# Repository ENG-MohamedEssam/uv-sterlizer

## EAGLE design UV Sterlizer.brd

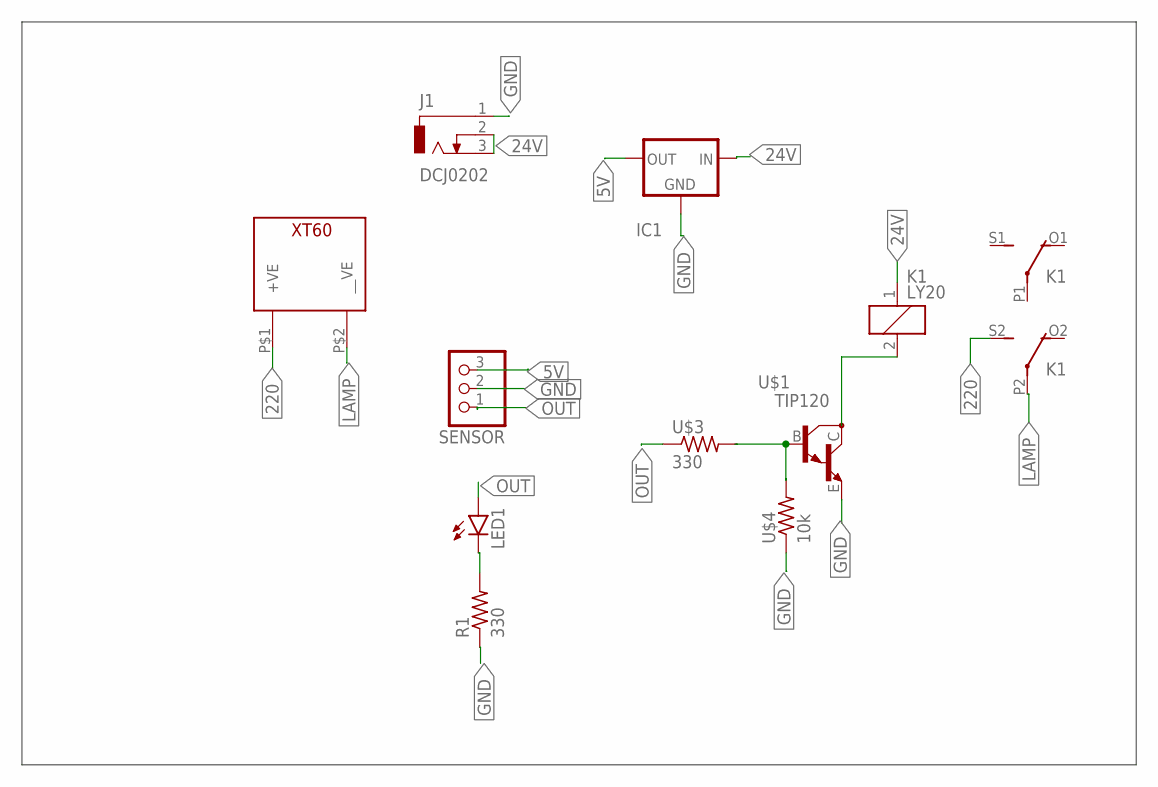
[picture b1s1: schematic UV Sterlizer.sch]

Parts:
IC1: 78XX-METAL; TO3-79
J1: DCJ0202
K1: LY20
LED1: LED5MM
R1: 330; 0204/7
SENSOR: PINHD-1X3; 1X03
U$1: TIP120
U$3: 330; 0207/10
U$4: 10k; 0207/10
U$5: XT60_CONNECTOR; XT60

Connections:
5V: IC1.1 (OUT), SENSOR.3
24V: IC1.3 (IN), J1.2, J1.3, K1.1
220: K1.S2 (S), U$5.P$1 (+VE)
GND: IC1.2 (GND), J1.1, R1.1, SENSOR.2, U$1.E, U$4.1
LAMP: K1.P2, U$5.P$2 (__VE)
unnamed: K1.2, U$1.C
unnamed: U$1.B, U$3.2, U$4.2
unnamed: LED1.K (C), R1.2
OUT: LED1.A, SENSOR.1, U$3.1

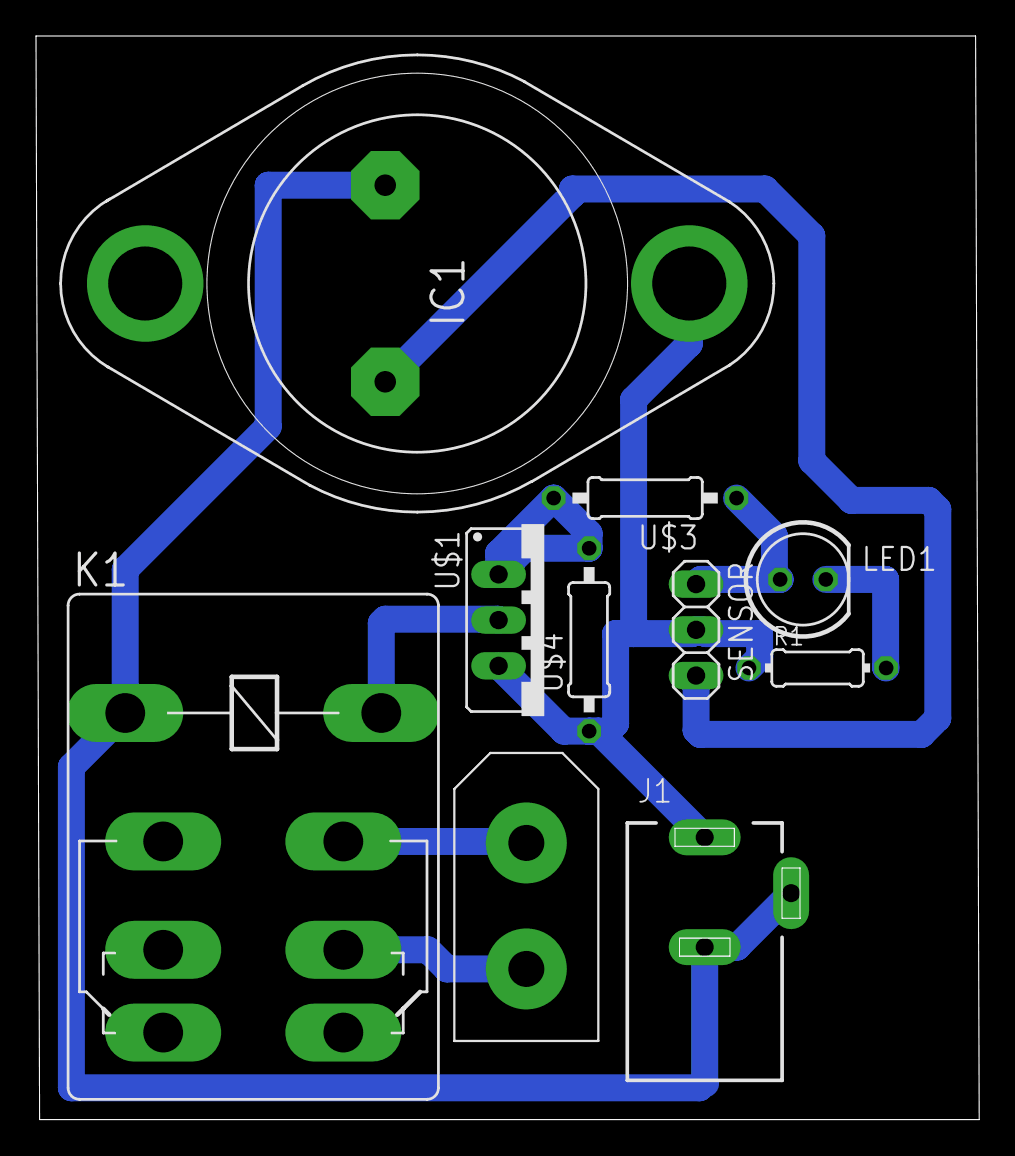
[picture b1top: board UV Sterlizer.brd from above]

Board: 2 copper layers, 52.4 x 60.2 mm, 10 parts (0 on the bottom side), 9 nets.

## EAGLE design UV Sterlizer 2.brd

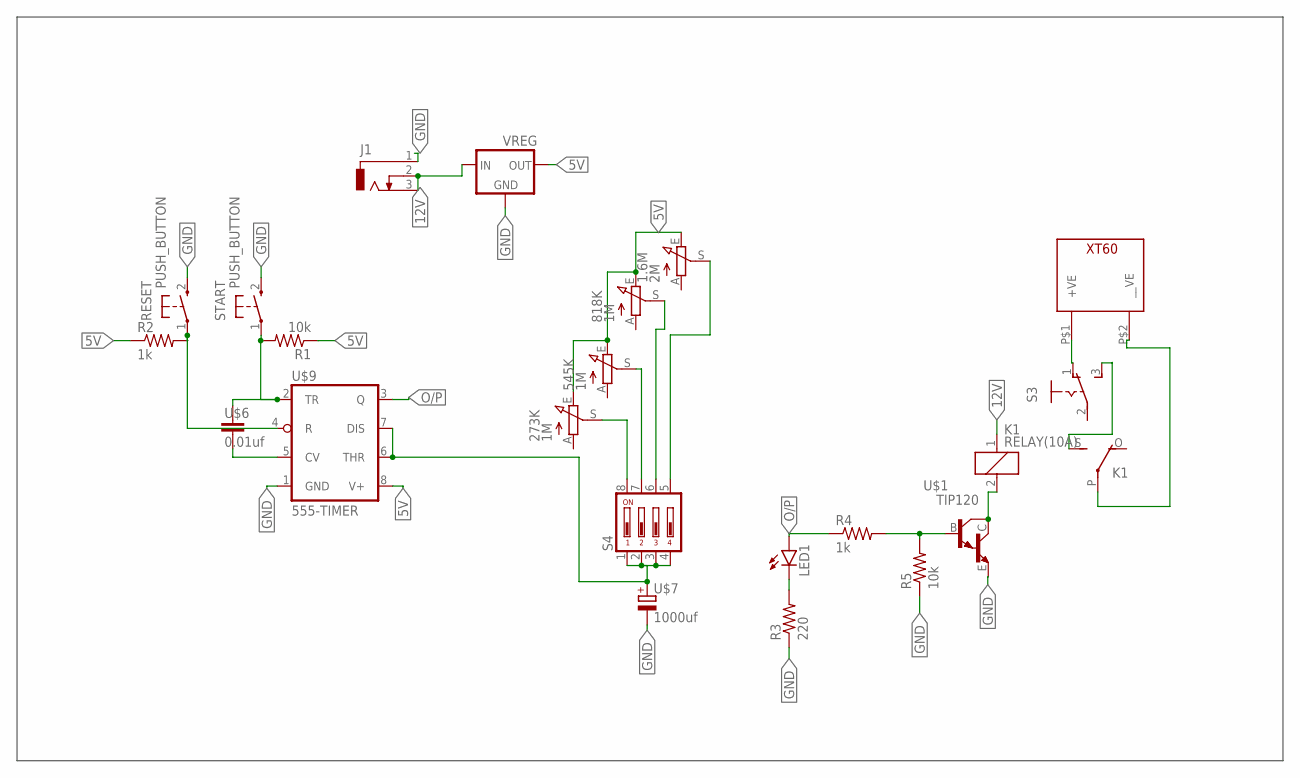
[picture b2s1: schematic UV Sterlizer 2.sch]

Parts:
1.6M: 2M; RJ9W
273K, 545K, 818K: 1M; RJ9W
J1: DCJ0303
K1: RELAY(10A); G5LE
LED1: LED5MM
R1, R5: 10k; 0204/7
R2, R4: 1k; 0204/7
R3: 220; 0204/7
RESET: PUSH_BUTTON; B3F-10XX
S3: SLIDING_SWITCH; 255SB
S4: DS04; DS-04
START: PUSH_BUTTON; B3F-10XX
U$1: TIP120
U$6: 0.01uf; C025-025X050
U$7: 1000uf; E3,5-8
U$8: XT60_CONNECTOR; XT60
U$9: 555-TIMER; DIL08
VREG: 78XX-METAL; TO3-79

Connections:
5V: 1.6M.E, 273K.E, 545K.E, 818K.E, R1.1, R2.1, U$9.8 (V+), VREG.1 (OUT)
12V: J1.2, J1.3, K1.1, VREG.3 (IN)
GND: J1.1, R3.1, R5.1, RESET.2 (S), START.2 (S), U$1.E, U$7.-, U$9.1 (GND), VREG.2 (GND)
unnamed: K1.2, U$1.C
unnamed: R4.2, R5.2, U$1.B
unnamed: K1.S, S3.3 (S)
unnamed: K1.P, U$8.P$2 (__VE)
unnamed: R1.2, START.1, U$6.1, U$9.2 (TR)
unnamed: LED1.K (C), R3.2
unnamed: 273K.S, S4.8
unnamed: 545K.S, S4.7
unnamed: 818K.S, S4.6
unnamed: 1.6M.S, S4.5
unnamed: S3.1 (O), U$8.P$1 (+VE)
unnamed: S4.1, S4.2, S4.3, S4.4, U$7.+, U$9.6 (THR), U$9.7 (DIS)
unnamed: U$6.2, U$9.5 (CV)
unnamed: R2.2, RESET.1, U$9.4 (R)
O/P: LED1.A, R4.1, U$9.3 (Q)

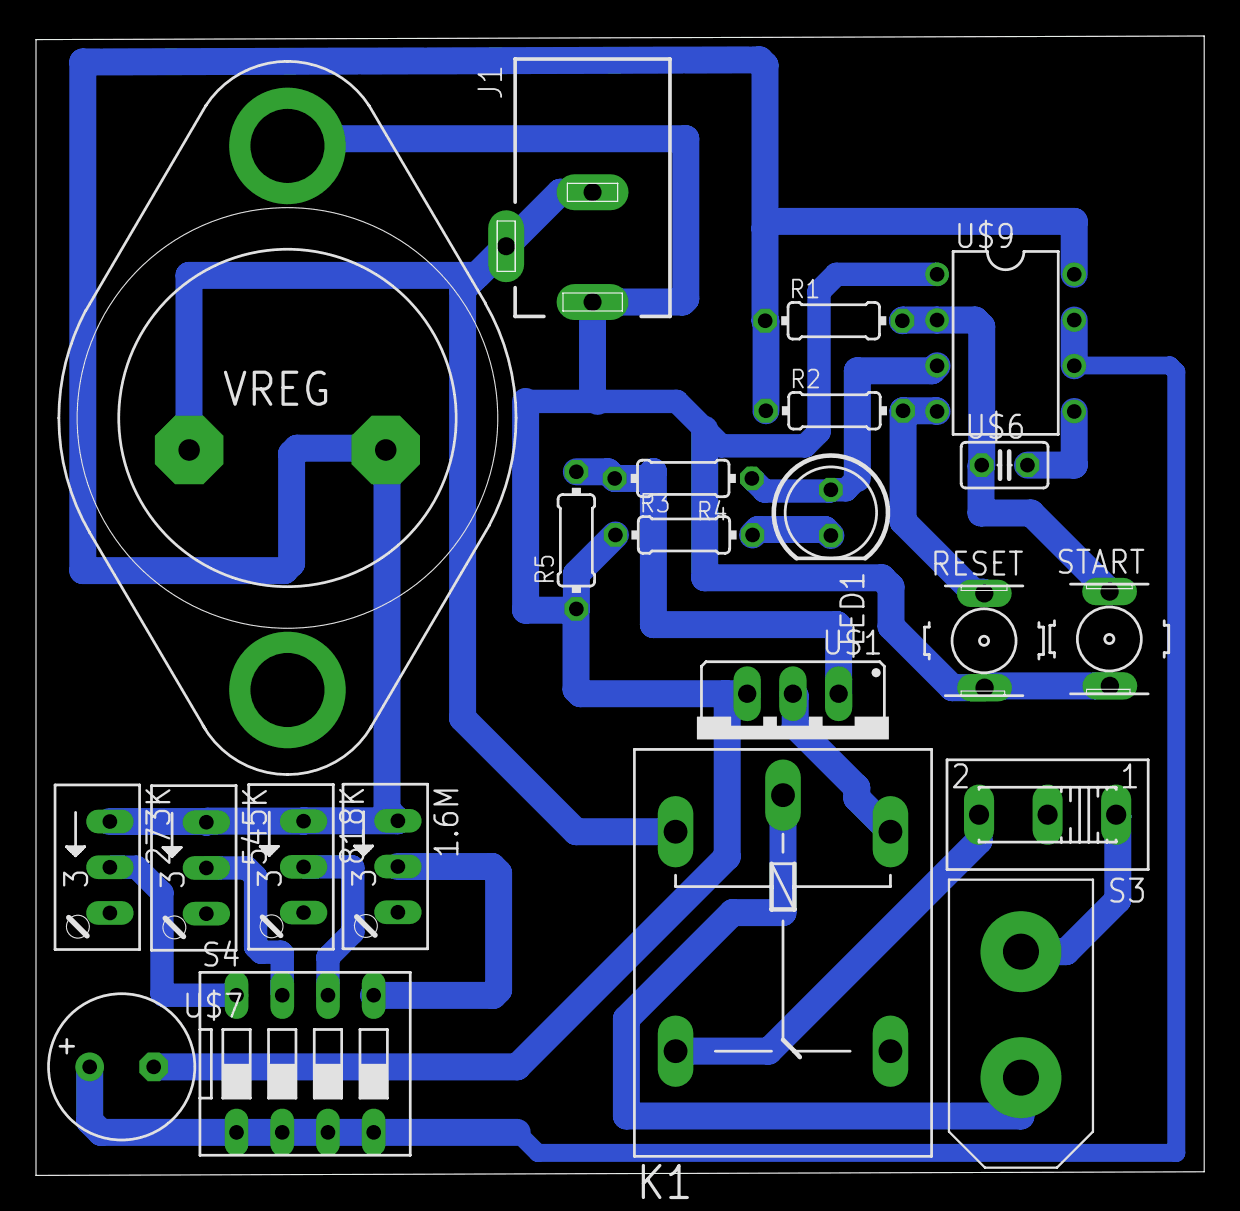
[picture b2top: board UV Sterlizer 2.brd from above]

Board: 2 copper layers, 64.9 x 63.3 mm, 22 parts (0 on the bottom side), 18 nets.
